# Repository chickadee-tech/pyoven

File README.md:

# Chickadee Tech pyoven #
This is a replacement control board for a [Breville 450XL](https://remanufactured.brevilleusa.com/collections/ovens/products/mini-smart-oven-rm-bov450xl?variant=615248833),
their smallest toaster oven. Its meant to enable programming the oven using CircuitPython. It can
then be used for food or reflowing PCBs but do not mix the two in the same oven.

DO NOT leave the oven unattended!

## Contributing ##
Please note that this project is released with a [Contributor Code of Conduct](CODE_OF_CONDUCT.md). By participating in this project you agree to abide by its terms.

### Setup ###
Components and footprints for PCB parts are not included in this repository. Instead, checkout the [chickadee-tech/kicad-libs](https://github.com/chickadee-tech/kicad-libs) repository in the same directory that this repository is checked out in. All part definitions should be relative so that they will load correctly.

### Pull requests ###
For fixes please submit a pull request to the original repository.

### Derivatives ###
If developing your own version of the spacer board please remove all Chickadee Tech trademarks and follow the [CC-BY license](LICENSE). While not required, please consider open sourcing your modifications so others can learn from your improvements.

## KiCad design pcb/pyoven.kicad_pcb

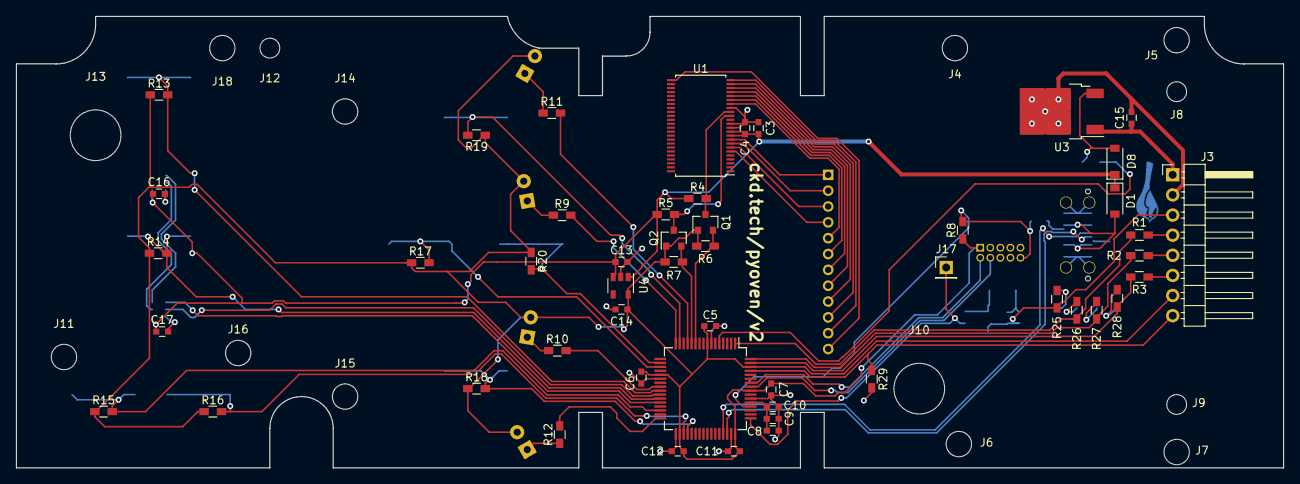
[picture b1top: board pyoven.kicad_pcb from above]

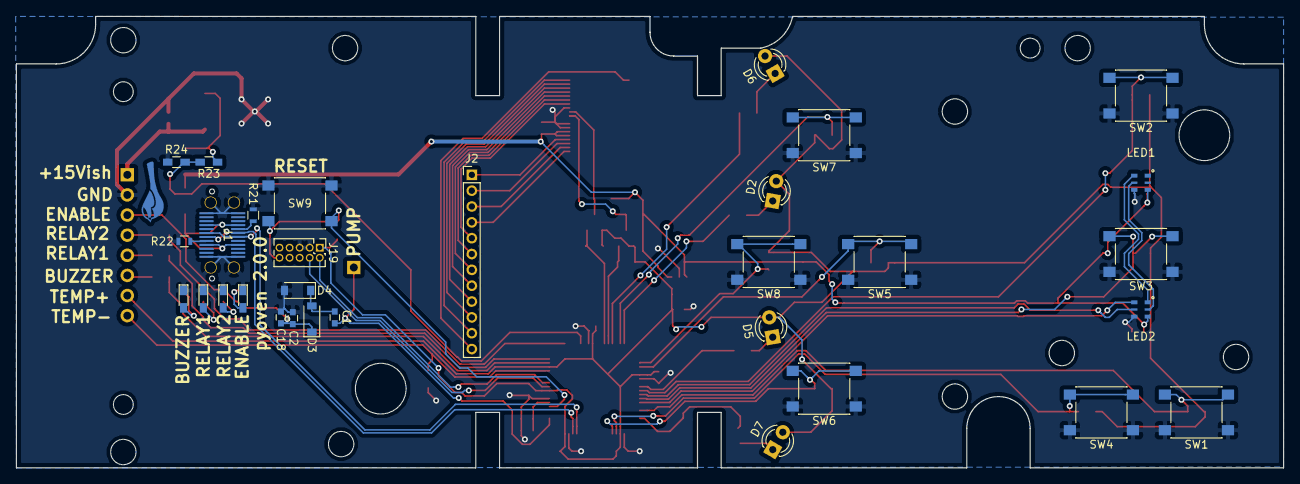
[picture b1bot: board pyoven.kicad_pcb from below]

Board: 2 copper layers, 160.0 x 57.0 mm, 95 parts (31 on the bottom side), 65 nets.

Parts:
C1, C3, C4, C5, C6, C7, C10, C11, C12, C16, C17: 0.1uF; C_0603
C2, C8, C18: 10uF; C_0603
C9, C13, C14, C15: 1uF; C_0603
D1, D3, D4, D8: MBR120; D_SOD-123
D2, D5, D6, D7: LED_Small_ALT; LED_D3.0mm
D9, D10, D11, D12: SMD; LED_0603_HandSoldering
J1: USB_C_Receptacle; DX07S024WJ3-OSHPARK-HS
J2: Conn_01x12; Pin_Header_Straight_1x12_Pitch2.00mm
J3: Conn_01x08; Pin_Header_Angled_1x08_Pitch2.54mm
J4, J5, J6, J7, J11, J14, J15, J16, J18: Conn_01x01; MountingHole_3.2mm_M3
J8, J9, J12: Conn_01x01; MountingHole_2.5mm
J10, J13: Conn_01x01; MountingHole_6.4mm_M6
J17: Conn_01x01; Pin_Header_Straight_1x01_Pitch2.54mm
J19: Conn_02x05_Odd_Even; Pin_Header_Straight_2x05_Pitch1.27mm
LED1, LED2: APA102; APA102-2020
Q1, Q2: BSS138; SOT-23
R1, R2, R3, R24: 3.3k; R_0603_HandSoldering
R4, R5, R6, R7: 4.7k; R_0603_HandSoldering
R8, R13, R14, R15, R16, R17, R18, R19, R20, R29: 10k; R_0603_HandSoldering
R9, R10, R11, R12, R25, R26, R27, R28: 1k; R_0603_HandSoldering
R21, R22: 5.1k; R_0603
R23: 2.2k; R_0603_HandSoldering
SW1: Frozen; SW_SPST_PTS645
SW2: More; SW_SPST_PTS645
SW3: Start; SW_SPST_PTS645
SW4: C/F; SW_SPST_PTS645
SW5: Dec; SW_SPST_PTS645
SW6: Temp; SW_SPST_PTS645
SW7: Time; SW_SPST_PTS645
SW8: Inc; SW_SPST_PTS645
SW9: Reset; SW_SPST_PTS645
U1: PCF8551ATT; TSSOP-48_6.1x12.5mm_Pitch0.5mm
U2: SAMD51J; TQFP-64_10x10mm_Pitch0.5mm
U3: L7805; TO-252-2
U4: AP2204K-1.5; SOT-23-5

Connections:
+3V3: C5.2, C6.1, C7.2, C11.2, C12.2, C14.1, D2.2, D5.2, D6.2, D7.2, J3.7, J19.1, Q1.1, Q2.1, R6.1, R7.1, R8.1, R13.1, R14.1, R15.1, R16.1, R17.1, R18.1, R19.1, R20.1, U2.8, U2.21, U2.34, U2.48, U2.56, U2.62, U4.5
+5V: C3.1, C4.1, C13.1, C16.1, C17.1, D1.1, D8.1, LED1.3, LED2.3, R4.1, R5.1, U1.10, U1.11, U4.1, U4.3
+VDC: C15.1, J3.1, U3.1
/BUZZER: R3.2, R28.1, U2.63
/CI: LED2.5, U2.26
/CO: LED1.5, LED2.2
/COM0: J2.4, U1.6
/COM1: J2.3, U1.7
/COM2: J2.2, U1.8
/COM3: J2.1, U1.9
/D+: J1.A6, J1.B6, U2.46
/D-: J1.A7, J1.B7, U2.45
/DEC: R17.2, SW5.2, U2.19
/DI: LED2.6, U2.28
/DO: LED1.6, LED2.1
/ENABLE: C2.1, C18.1, D3.1, J3.3, R25.1
/FAR_LEFT_LED: R12.2, U2.32
/FAR_RIGHT_LED: R11.2, U2.13
/FROZEN: R15.2, SW1.2, U2.30
/INC: R20.2, SW8.2, U2.18
/LEFT_LED: R10.2, U2.24
/MORE: R13.2, SW2.2, U2.25
/PUMP: C1.2, J17.1, U2.49
/RELAY1: R2.2, R27.1, U2.64
/RELAY2: R1.2, R26.1, U2.1
/RIGHT_LED: R9.2, U2.16
/SCL_3V: Q2.2, R7.2, U2.12
/SCL_5V: Q2.3, R5.2, U1.15
/SDA_3V: Q1.2, R6.2, U2.11
/SDA_5V: Q1.3, R4.2, U1.16
/SEG0: J2.5, U1.18
/SEG1: J2.6, U1.19
/SEG2: J2.7, U1.20
/SEG3: J2.8, U1.21
/SEG4: J2.9, U1.22
/SEG5: J2.10, U1.23
/SEG6: J2.11, U1.24
/SEG7: J2.12, U1.25
/START: R14.2, SW3.2, U2.27
/SWDCLK: J19.4, U2.57
/SWDIO: J19.2, U2.58
/TEMP: R18.2, SW6.2, U2.36
/TEMP-: J3.8, R29.1, U2.61
/TIME: R19.2, SW7.2, U2.15
/TOASTER_5V: D8.2, R23.1, U3.3
/UNITS: R16.2, SW4.2, U2.35
/nReset: J19.10, R8.2, SW9.2, U2.52
GNDPWR: C2.2, C3.2, C4.2, C5.1, C6.2, C7.1, C8.2, C9.2, C10.2, C11.1, C12.1, C13.2, C14.2, C15.2, C16.2, C17.2, C18.2, D4.2, D9.1, D10.1, D11.1, D12.1, J1.A1, J1.A12, J1.B1, J1.B12, J1.S1, J3.2, J19.3, J19.5, LED1.4, LED2.4, R21.2, R22.2, R24.2, R29.2, SW1.1, SW2.1, SW3.1, SW4.1, SW5.1, SW6.1, SW7.1, SW8.1, SW9.1, U1.12, U1.13, U1.17, U2.7, U2.22, U2.33, U2.47, U2.54, U3.2, U4.2
unnamed: C1.1, D3.2, D4.1
unnamed: C8.1, C9.1, C10.1, U2.53
unnamed: D1.2, J1.A4, J1.A9, J1.B4, J1.B9
unnamed: D2.1, R9.1
unnamed: D5.1, R10.1
unnamed: D6.1, R11.1
unnamed: D7.1, R12.1
unnamed: D9.2, R25.2
unnamed: D10.2, R26.2
unnamed: D11.2, R27.2
unnamed: D12.2, R28.2
unnamed: J1.A5, R22.1
unnamed: J1.B5, R21.1
unnamed: J3.4, R1.1
unnamed: J3.5, R2.1
unnamed: J3.6, R3.1
unnamed: R23.2, R24.1, U2.5

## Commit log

2018-01-06 Initial version. Ordered from OSH Park.
2018-07-25 A number of fixes: * lcd pin swap * button location tweak * temp divider resistor * correct regulator footprint
